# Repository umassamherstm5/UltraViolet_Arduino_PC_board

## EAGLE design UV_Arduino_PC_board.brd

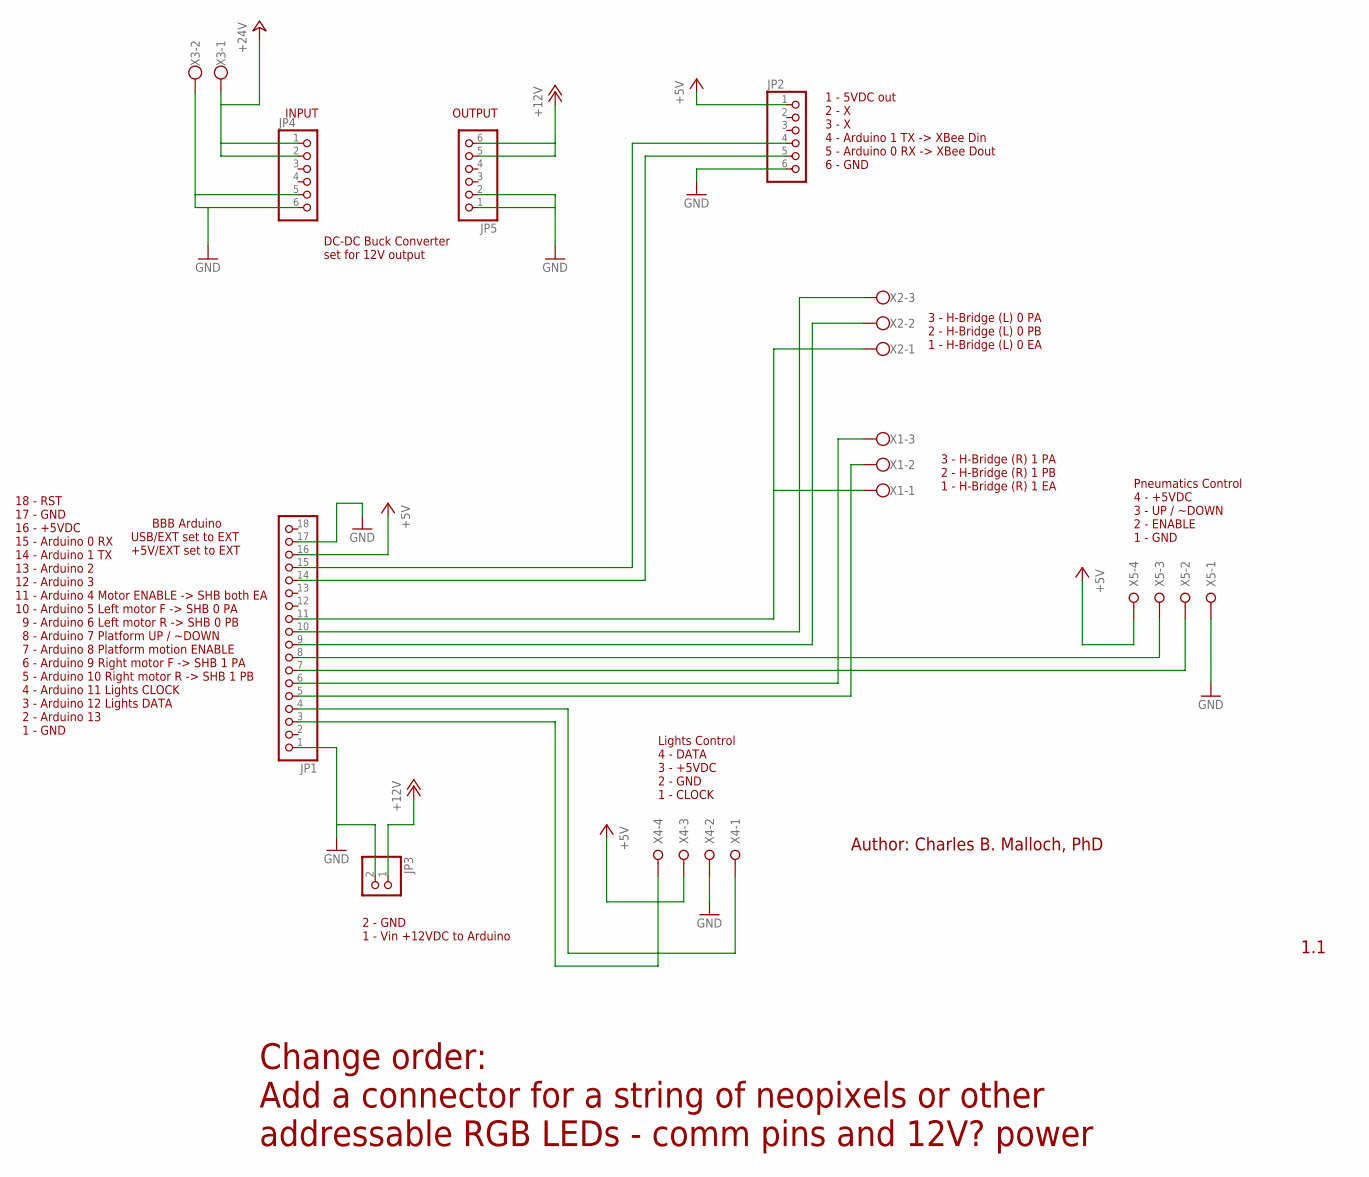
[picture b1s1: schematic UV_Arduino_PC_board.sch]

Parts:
JP1: PINHD-1X18; 1X18
JP2, JP4, JP5: PINHD-1X6; 1X06
JP3: PINHD-1X2; 1X02
X1, X2: W237-103
X3: W237-102
X4, X5: W237-04P; W237-4P

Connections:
+5V: JP1.16, JP2.1, X4.3, X5.4
+12V: JP3.1, JP5.5, JP5.6
GND: JP1.1, JP1.17, JP2.6, JP3.2, JP4.5, JP4.6, JP5.1, JP5.2, X3.2, X4.2, X5.1
unnamed: JP4.1, JP4.2, X3.1
unnamed: JP1.14, JP2.5
unnamed: JP1.4, X4.1
unnamed: JP1.3, X4.4
unnamed: JP1.11, X1.1, X2.1
unnamed: JP1.10, X2.3
unnamed: JP1.9, X2.2
unnamed: JP1.6, X1.3
unnamed: JP1.5, X1.2
unnamed: JP1.15, JP2.4
unnamed: JP1.8, X5.3
unnamed: JP1.7, X5.2

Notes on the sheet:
1 - 5VDC out 2 - X 3 - X 4 - Arduino 1 TX -> XBee Din 5 - Arduino 0 RX -> XBee Dout 6 - GND
3 - H-Bridge (L) 0 PA 2 - H-Bridge (L) 0 PB 1 - H-Bridge (L) 0 EA
3 - H-Bridge (R) 1 PA 2 - H-Bridge (R) 1 PB 1 - H-Bridge (R) 1 EA
BBB Arduino USB/EXT set to EXT +5V/EXT set to EXT
DC-DC Buck Converter set for 12V output
18 - RST 17 - GND 16 - +5VDC 15 - Arduino 0 RX 14 - Arduino 1 TX 13 - Arduino 2 12 - Arduino 3 11 - Arduino 4 Motor ENABLE -> SHB both EA 10 - Arduino 5 Left motor F -> SHB 0 PA 9 - Arduino 6 Left motor R -> SHB 0 PB 8 - Arduino 7 Platform UP / ~DOWN 7 - Arduino 8 Platform motion ENABLE 6 - Arduino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
2 - GND 1 - Vin +12VDC to Arduino
INPUT
OUTPUT
Pneumatics Control 4 - +5VDC 3 - UP / ~DOWN 2 - ENABLE 1 - GND
Author: Charles B. Malloch, PhD
1.1
Change order: Add a connector for a string of neopixels or other addressable RGB LEDs - comm pins and 12V? power
Lights Control 4 - DATA 3 - +5VDC 2 - GND 1 - CLOCK

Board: 2 copper layers, 10 parts (0 on the bottom side), 15 nets, no tracks yet.

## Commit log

2014-10-22 Added circuit board
2014-10-22 Added name to schematic
2014-10-23 Changed layout to fit actual board
    Added change order to allow for a string of LEDs
2014-10-25 Added lights control terminals
    to control a LED strip with WS2811 or WS2812 controlled individually
    addressable LEDs
2014-10-25 Files now in Eagle v7.1.0 format
    fixed some comments and adjusted to match the actual build.
2015-03-31 Add connector for neopixels
